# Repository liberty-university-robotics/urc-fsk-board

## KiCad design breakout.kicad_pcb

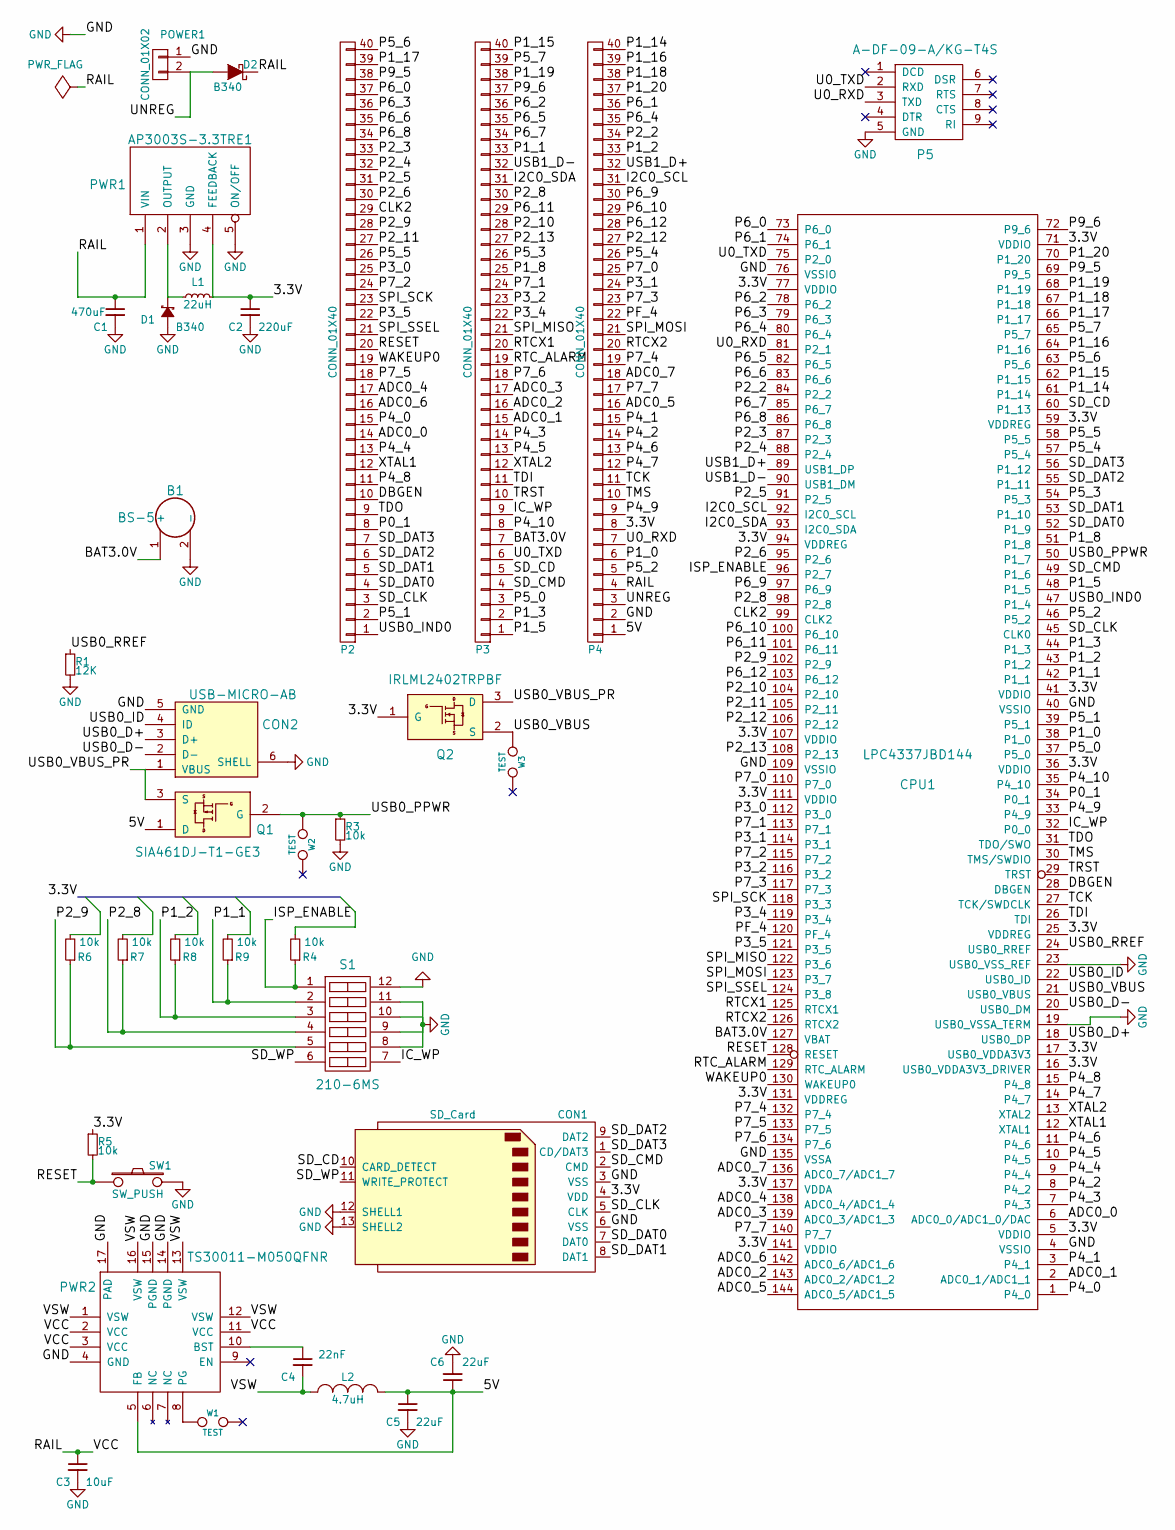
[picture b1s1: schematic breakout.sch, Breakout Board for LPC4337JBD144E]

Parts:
B1: BS-5
C1: 470uF; Elko_vert_25x12.5mm_RM5_CopperClear
C2: 220uF; TantalC_SizeB_EIA-3528_Reflow
C3: 10uF; TantalC_SizeC_EIA-6032_Reflow
C4: 22nF; C_0402
C5, C6: 22uF; C_0805
CON1: SD_Card; SD_MMC_Card_Receptacle
CON2: USB-MICRO-AB; USB_MICRO_AB
CPU1: LPC4337JBD144; LQFP-144_20x20mm_Pitch0.5mm
D1, D2: B340; Diode-SMC_Standard
L1: 22uH; Choke_SMD_12x12mm_h8mm
L2: 4.7uH; C_1210
P2, P3, P4: CONN_01X40; Socket_Strip_Straight_1x40
P5: A-DF-09-A/KG-T4S; DIN9F
POWER1: CONN_01X02; 1792863
PWR1: AP3003S-3.3TRE1; TO-263-5
PWR2: TS30011-M050QFNR; QFN-16-1EP_3x3mm_Pitch0.5mm
Q1: SIA461DJ-T1-GE3; PowerPak_SC-70-6L-Single
Q2: IRLML2402TRPBF; SOT-23
R1: 12K; R_0603
R3, R4, R5, R6, R7, R8, R9: 10k; R_0402
S1: 210-6MS; SW_DIP_x6_Slide
SW1: SW_PUSH; 1825910-7
W1, W2, W3: TEST; Measurement_Point_Round-SMD-Pad_Small

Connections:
/3.3V: C2.1, CON1.4 (VDD), CPU1.5 (VDDIO), CPU1.16 (USB0_VDDA3V3_DRIVER), CPU1.17 (USB0_VDDA3V3), CPU1.25 (VDDREG), CPU1.36 (VDDIO), CPU1.41 (VDDIO), CPU1.59 (VDDREG), CPU1.71 (VDDIO), CPU1.77 (VDDIO), CPU1.94 (VDDREG), CPU1.107 (VDDIO), CPU1.111 (VDDIO), CPU1.131 (VDDREG), CPU1.137 (VDDA), CPU1.141 (VDDIO), L1.2, P4.8, PWR1.4 (FEEDBACK), Q2.1 (G), R5.1
/5V: C5.1, C6.1, L2.2, P4.1, PWR2.5 (FB), Q1.1 (D)
/ADC0_0: CPU1.6 (ADC0_0/ADC1_0/DAC), P2.14
/ADC0_1: CPU1.2 (ADC0_1/ADC1_1), P3.15
/ADC0_2: CPU1.143 (ADC0_2/ADC1_2), P3.16
/ADC0_3: CPU1.139 (ADC0_3/ADC1_3), P3.17
/ADC0_4: CPU1.138 (ADC0_4/ADC1_4), P2.17
/ADC0_5: CPU1.144 (ADC0_5/ADC1_5), P4.16
/ADC0_6: CPU1.142 (ADC0_6/ADC1_6), P2.16
/ADC0_7: CPU1.136 (ADC0_7/ADC1_7), P4.18
/BAT3.0V: B1.1 (+), CPU1.127 (VBAT), P3.7
/CLK2: CPU1.99 (CLK2), P2.29
/DBGEN: CPU1.28 (DBGEN), P2.10
/I2C0_SCL: CPU1.92 (I2C0_SCL), P4.31
/I2C0_SDA: CPU1.93 (I2C0_SDA), P3.31
/IC_WP: CPU1.32 (P0_0), P3.9, S1.7
/ISP_ENABLE: CPU1.96 (P2_7), R4.1, S1.1
/P0_1: CPU1.34 (P0_1), P2.8
/P1_0: CPU1.38 (P1_0), P4.6
/P1_1: CPU1.42 (P1_1), P3.33, R9.1, S1.2
/P1_2: CPU1.43 (P1_2), P4.33, R8.1, S1.3
/P1_3: CPU1.44 (P1_3), P3.2
/P1_5: CPU1.48 (P1_5), P3.1
/P1_8: CPU1.51 (P1_8), P3.25
/P1_14: CPU1.61 (P1_14), P4.40
/P1_15: CPU1.62 (P1_15), P3.40
/P1_16: CPU1.64 (P1_16), P4.39
/P1_17: CPU1.66 (P1_17), P2.39
/P1_18: CPU1.67 (P1_18), P4.38
/P1_19: CPU1.68 (P1_19), P3.38
/P1_20: CPU1.70 (P1_20), P4.37
/P2_2: CPU1.84 (P2_2), P4.34
/P2_3: CPU1.87 (P2_3), P2.33
/P2_4: CPU1.88 (P2_4), P2.32
/P2_5: CPU1.91 (P2_5), P2.31
/P2_6: CPU1.95 (P2_6), P2.30
/P2_8: CPU1.98 (P2_8), P3.30, R7.1, S1.4
/P2_9: CPU1.102 (P2_9), P2.28, R6.1, S1.5
/P2_10: CPU1.104 (P2_10), P3.28
/P2_11: CPU1.105 (P2_11), P2.27
/P2_12: CPU1.106 (P2_12), P4.27
/P2_13: CPU1.108 (P2_13), P3.27
/P3_0: CPU1.112 (P3_0), P2.25
/P3_1: CPU1.114 (P3_1), P4.24
/P3_2: CPU1.116 (P3_2), P3.23
/P3_4: CPU1.119 (P3_4), P3.22
/P3_5: CPU1.121 (P3_5), P2.22
/P4_0: CPU1.1 (P4_0), P2.15
/P4_1: CPU1.3 (P4_1), P4.15
/P4_2: CPU1.8 (P4_2), P4.14
/P4_3: CPU1.7 (P4_3), P3.14
/P4_4: CPU1.9 (P4_4), P2.13
/P4_5: CPU1.10 (P4_5), P3.13
/P4_6: CPU1.11 (P4_6), P4.13
/P4_7: CPU1.14 (P4_7), P4.12
/P4_8: CPU1.15 (P4_8), P2.11
/P4_9: CPU1.33 (P4_9), P4.9
/P4_10: CPU1.35 (P4_10), P3.8
/P5_0: CPU1.37 (P5_0), P3.3
/P5_1: CPU1.39 (P5_1), P2.2
/P5_2: CPU1.46 (P5_2), P4.5
/P5_3: CPU1.54 (P5_3), P3.26
/P5_4: CPU1.57 (P5_4), P4.26
/P5_5: CPU1.58 (P5_5), P2.26
/P5_6: CPU1.63 (P5_6), P2.40
/P5_7: CPU1.65 (P5_7), P3.39
/P6_0: CPU1.73 (P6_0), P2.37
/P6_1: CPU1.74 (P6_1), P4.36
/P6_2: CPU1.78 (P6_2), P3.36
/P6_3: CPU1.79 (P6_3), P2.36
/P6_4: CPU1.80 (P6_4), P4.35
/P6_5: CPU1.82 (P6_5), P3.35
/P6_6: CPU1.83 (P6_6), P2.35
/P6_7: CPU1.85 (P6_7), P3.34
/P6_8: CPU1.86 (P6_8), P2.34
/P6_9: CPU1.97 (P6_9), P4.30
/P6_10: CPU1.100 (P6_10), P4.29
/P6_11: CPU1.101 (P6_11), P3.29
/P6_12: CPU1.103 (P6_12), P4.28
/P7_0: CPU1.110 (P7_0), P4.25
/P7_1: CPU1.113 (P7_1), P3.24
/P7_2: CPU1.115 (P7_2), P2.24
/P7_3: CPU1.117 (P7_3), P4.23
/P7_4: CPU1.132 (P7_4), P4.19
/P7_5: CPU1.133 (P7_5), P2.18
/P7_6: CPU1.134 (P7_6), P3.18
/P7_7: CPU1.140 (P7_7), P4.17
/P9_5: CPU1.69 (P9_5), P2.38
/P9_6: CPU1.72 (P9_6), P3.37
/PF_4: CPU1.120 (PF_4), P4.22
/RAIL: C1.1, C3.1, D2.2 (K), P4.4, PWR1.1 (VIN), PWR2.2 (VCC), PWR2.3 (VCC), PWR2.11 (VCC)
/RESET: CPU1.128 (RESET), P2.20, R5.2, SW1.1
/RTCX1: CPU1.125 (RTCX1), P3.20
/RTCX2: CPU1.126 (RTCX2), P4.20
/RTC_ALARM: CPU1.129 (RTC_ALARM), P3.19
/SD_CD: CON1.10 (CARD_DETECT), CPU1.60 (P1_13), P3.5
/SD_CLK: CON1.5 (CLK), CPU1.45 (CLK0), P2.3
/SD_CMD: CON1.2 (CMD), CPU1.49 (P1_6), P3.4
/SD_DAT0: CON1.7 (DAT0), CPU1.52 (P1_9), P2.4
/SD_DAT1: CON1.8 (DAT1), CPU1.53 (P1_10), P2.5
/SD_DAT2: CON1.9 (DAT2), CPU1.55 (P1_11), P2.6
/SD_DAT3: CON1.1 (CD/DAT3), CPU1.56 (P1_12), P2.7
/SD_WP: CON1.11 (WRITE_PROTECT), S1.6
/SPI_MISO: CPU1.122 (P3_6), P3.21
/SPI_MOSI: CPU1.123 (P3_7), P4.21
/SPI_SCK: CPU1.118 (P3_3), P2.23
/SPI_SSEL: CPU1.124 (P3_8), P2.21
/TCK: CPU1.27 (TCK/SWDCLK), P4.11
/TDI: CPU1.26 (TDI), P3.11
/TDO: CPU1.31 (TDO/SWO), P2.9
/TMS: CPU1.30 (TMS/SWDIO), P4.10
/TRST: CPU1.29 (TRST), P3.10
/U0_RXD: CPU1.81 (P2_1), P4.7, P5.3 (TXD)
/U0_TXD: CPU1.75 (P2_0), P3.6, P5.2 (RXD)
/UNREG: D2.1 (A), P4.3, POWER1.2
/USB0_D+: CON2.3 (D+), CPU1.18 (USB0_DP)
/USB0_D-: CON2.2 (D-), CPU1.20 (USB0_DM)
/USB0_ID: CON2.4 (ID), CPU1.22 (USB0_ID)
/USB0_IND0: CPU1.47 (P1_4), P2.1
/USB0_PPWR: CPU1.50 (P1_7), Q1.2 (G), R3.1, W2.1
/USB0_RREF: CPU1.24 (USB0_RREF), R1.1
/USB0_VBUS: CPU1.21 (USB0_VBUS), Q2.2 (S), W3.1
/USB0_VBUS_PR: CON2.1 (VBUS), Q1.3 (S), Q2.3 (D)
/USB1_D+: CPU1.89 (USB1_DP), P4.32
/USB1_D-: CPU1.90 (USB1_DM), P3.32
/VSW: C4.2, L2.1, PWR2.1 (VSW), PWR2.12 (VSW), PWR2.13 (VSW), PWR2.16 (VSW)
/WAKEUP0: CPU1.130 (WAKEUP0), P2.19
/XTAL1: CPU1.12 (XTAL1), P2.12
/XTAL2: CPU1.13 (XTAL2), P3.12
GND: B1.2 (-), C1.2, C2.2, C3.2, C5.2, C6.2, CON1.3 (VSS), CON1.6 (VSS), CON1.12 (SHELL1), CON1.13 (SHELL2), CON2.5 (GND), CON2.6 (SHELL), CPU1.4 (VSSIO), CPU1.19 (USB0_VSSA_TERM), CPU1.23 (USB0_VSS_REF), CPU1.40 (VSSIO), CPU1.76 (VSSIO), CPU1.109 (VSSIO), CPU1.135 (VSSA), D1.1 (A), P4.2, P5.5 (GND), POWER1.1, PWR1.3 (GND), PWR1.5 (ON/OFF), PWR2.4 (GND), PWR2.14 (PGND), PWR2.15 (PGND), PWR2.17 (PAD), R1.2, R3.2, S1.8, S1.9, S1.10, S1.11, S1.12, SW1.2; also elsewhere on the board
unnamed: C4.1, PWR2.10 (BST)
unnamed: D1.2 (C), L1.1, PWR1.2 (OUTPUT)
unnamed: PWR2.8 (PG), W1.1

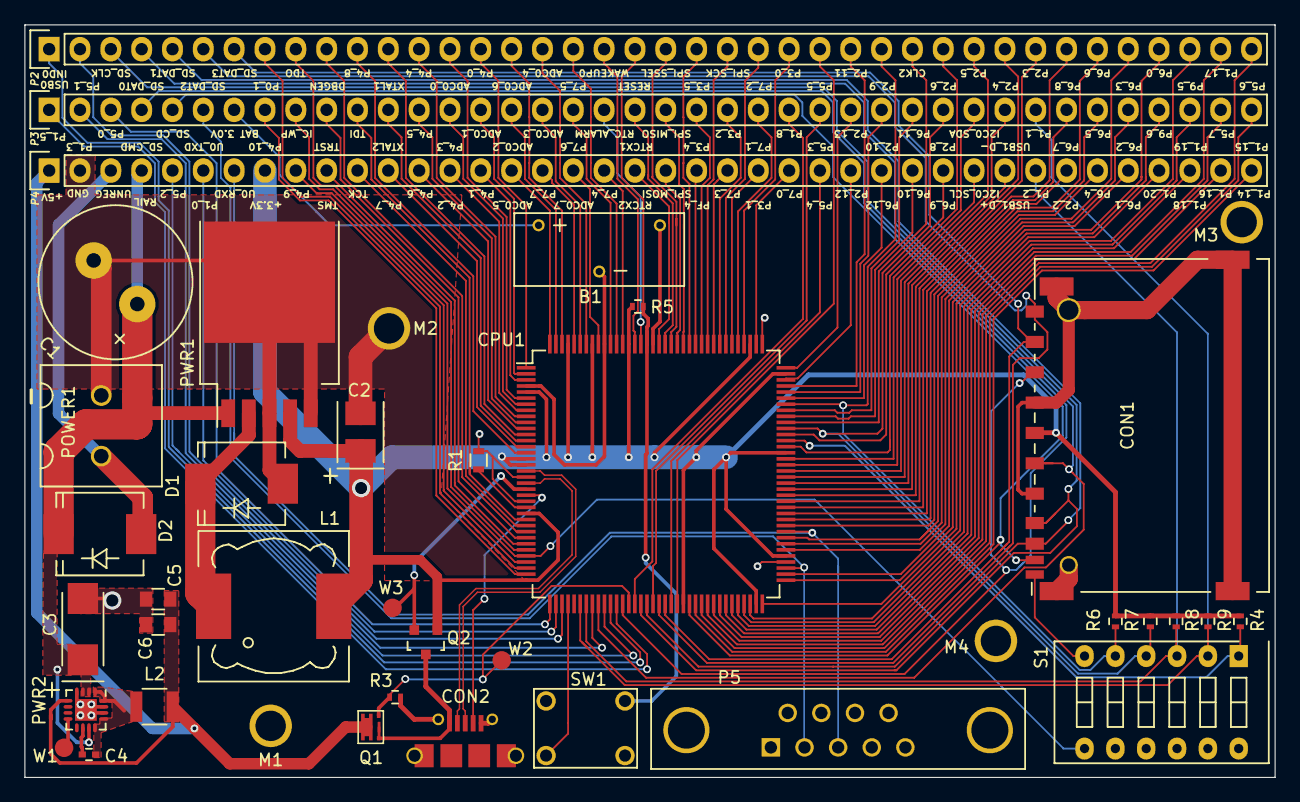
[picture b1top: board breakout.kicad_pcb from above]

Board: 2 copper layers, 103.0 x 62.0 mm, 40 parts (0 on the bottom side), 133 nets.

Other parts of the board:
M1, M2, M3, M4: MOUNTING_HOLE; MOUNTING_HOLE_2.5mm

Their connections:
GND: M1.1, M2.1, M3.1, M4.1; also elsewhere on the board

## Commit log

2015-10-07 added more components
2015-10-07 created a footprint library
2015-10-07 adding components
2015-10-14 added components to the library
2015-10-14 added SD card footprint
2015-10-14 working up a netlist of components
2015-10-14 added sd card slot and SPI pins to schematic
2015-10-15 added USB_MINI_AB_SMD footprint
2015-10-21 added circuit elements to the custom library
2015-10-21 added more footprints
2015-10-21 syncing pcb layout with schematic
2015-10-22 improved components
2015-10-22 added boot select pins
2015-10-22 fixed some more components
2015-10-27 adding components to the schematic, and fixing footprints
2015-10-28 updated netlist footprints to reflect breakout.cmp
2015-11-04 removed unecessary fuse, checked footprints
2015-11-06 added battery holder
2015-11-06 added battery to schematic
2015-11-08 cleaned out old traces, and set minimum track widths
2015-11-10 starting shuffle and board trace
2015-11-11 PCB: separated components and grouped by function
2015-11-11 set the design rules
2015-11-12 fixing net names
2015-11-12 added more nets
2015-11-12 fully netlisted CPU1
2015-11-12 traced 5V power regulator; removed uneeded components
2015-11-13 added 3.3V pad under CPU1
2015-11-16 layed out the power domain
2015-11-16 rough positioning of components
2015-11-16 more decisions on component placement
2015-11-17 set board edge and margin, and moved components around
2015-11-17 minor improvements
2015-11-18 locked components and switched USB0_PPWP to pin 50
2015-11-18 added polarity protection D2, and locked components
2015-11-18 routing IC left side traces
2015-11-23 top side of IC routed
2015-11-23 routed SD card socket and DIP switches
2015-11-23 routed lower-left of IC
2015-11-23 routed right side of IC
2015-11-23 fixed traces to the SD card connector
2015-11-23 routed left side of IC
2015-11-23 bottom side of IC routed
2015-11-30 increased size of ground plane
2015-12-01 routed the 3.3V lines to the microcontroller
2015-12-02 connected some grounds
2015-12-02 switched routes and connected power to DIP switch
2015-12-02 Edited some footprints to connect shell to ground
2015-12-05 Neatly organized schematic
2015-12-06 added thermal sink for 3.3reg
2015-12-06 added component and footprint for a FET
2015-12-06 improved 5V FET and added to schematic & board
2015-12-06 routed 5V FET
2015-12-06 added USB FET
2015-12-06 added USB FET to schematic and board
2015-12-06 added USB0_RREF and 12K resistor
2015-12-06 added the NC'd USB0 pins, and fixed some trace sizes
2015-12-06 added test points
2015-12-07 connected RESET to a header pin
2015-12-07 P1_1 & P1_2 to header; trace move to aid GND plane
2015-12-07 RAIL, UNREG, 5V
2015-12-07 added P1_3 and fixed annular ring of vias
2015-12-07 routed sub-IC traces
2015-12-07 routed USART0 and 3.3V to headers
2015-12-07 routed SD/MMC lines to headers
2015-12-07 shifted battery holder down
2015-12-07 checked SD/MMC footprint and fixed its annular ring size
2015-12-07 connected SD/MMC Receptacle's shell to GND
2015-12-07 checked and fixed USB_MICRO_AB footprint
2015-12-07 fixed silk size and a GND zone
2015-12-07 fixed soldermask clearance
2015-12-07 neatened zones around 5V regulatorr
2015-12-07 fixed ground plane clearance
2015-12-07 fixed annular ring sizes
2015-12-07 added mounting holes
2015-12-07 corrected LICENSE to CC-BY-SA (originally intended)
2015-12-07 added silk
2015-12-07 shifted pushbutton and usb micro receptacle up

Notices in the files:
breakout.kicad_pcb:
Copyright 2015 Liberty University
